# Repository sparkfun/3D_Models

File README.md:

3D Models for SparkFun Products!
----------------

This is a repository of basic geometry and source CAD files for 3D models that appear on our website. Models are stored in real world (1x) scale. STL units are millimeters.

_If you are using [eagleUp](https://eagleup.wordpress.com/) be sure to only export ```Place``` layers_

## Directory Structure

Folders and file names must only use a-z, - and _

#### Product Geometry Model Structure:
```
products/{product_id}/{rev_if_applicable}/{file_type}/

Ex:
products/12099/iges/12099.iges
products/12099/step/12099.step
products/12099/stl/12099.stl

If there were any revisions for this product_id:
products/11113/rev_1.0/stl/11113.stl
products/11113/rev_1.1/stl/11113.stl
```

#### Source Model Structure:
```
products/{product_id}/{rev_if_applicable}/source_{software}/

Ex:
products/11763/source_solidworks/model.sldprt

If there were any revisions for this product_id:
products/11763/rev_1.0/source_solidworks/11763.sldprt
products/11763/rev_1.1/source_solidworks/11763.sldprt

```

#### Product Display Structure:
We can display any combination of stl or json with textures
```
products/{product_id}/display/modela.stl

Ex:
products/8601/display/8601a.stl
products/8601/display/8601b.json
products/8601/display/8601b_texture.png
```

## Blender Common Display Materials

_Use the io_three blender addon in the https://github.com/mrdoob/three.js repository to export textured display models for our site_

_Be sure to set your scene's display device to none before export to prevent colors from being gamma corrected. Or use the startup file in this repo._

For composite display models, commit the blender file with separate objects for easy tweaking in the future. Combine the geometry before exporting to json.

#### Copper
```
Diffuse:  #DF8D38 Intensity: 0.8
Specular: #FFB730 Intensity: 0.5
Hardness: 100
```

#### Leads
```
Diffuse:  #FFFFFF Intensity: 0.8
Specular: #E6E6E6 Intensity: 0.5
Hardness: 100
```

#### Black Plastic (Headers)
```
Diffuse:  #000000 Intensity: 0.8
Specular: #A5A5A5 Intensity: 0.5
Hardness: 50
```

#### Black Metal 
```
Diffuse:  #000000 Intensity: 0.8
Specular: #505050 Intensity: 0.5
Hardness: 50
```

#### Black Chips
```
Diffuse:  #000000 Intensity: 1.0
Specular: #222222 Intensity: 0.5
Hardness: 50
```

#### SFE Red Silk
_Solid Material_
```
Diffuse:  #98041C Intensity: 1.0
Specular: #98041C Intensity: 0.5
Hardness: 50
```
_Textured Material_ (Red)
```
Diffuse:  #FF2835 Intensity: 0.8
Specular: #98041C Intensity: 0.5
Hardness: 50
```

#### Blue Plastic (Screw Terminals)
```
Diffuse:  #0000FF Intensity: 0.8
Specular: #0000A5 Intensity: 0.5
Hardness: 50
```

#### White Plastic
```
Diffuse:  #FFFFFF Intensity: 0.8
Specular: #E2E2E2 Intensity: 0.8
Hardness: 25
```

#### Grey Plastic
```
Diffuse:  #8A8A8A Intensity: 1.0
Specular: #FFFFFF Intensity: 0.25
Hardness: 50
```

#### Yellow Plastic (Li-ion Battery)
```
Diffuse:  #CC9D00 Intensity: 0.8
Specular: #FFD700 Intensity: 0.5
Hardness: 50
```

#### SMD Resistor Brown
```
Diffuse:  #8F5A24 Intensity: 0.8
Specular: #FFB730 Intensity: 0.5
Hardness: 100
```

#### Component Black
```
Diffuse:  #111111 Intensity: 0.8
Specular: #222222 Intensity: 0.5
Hardness: 100
```

#### Green Protoboard
```
Diffuse:  #00703D Intensity: 0.8
Specular: #0A5D19 Intensity: 0.5
Hardness: 100
```

#### TH Resistor
```
Diffuse:  #DBB37B Intensity: 0.8
Specular: #FFBA59 Intensity: 0.5
Hardness: 100
```

#### Yellow Tinted (SMD LED) 
```
Diffuse:  #CCC48E Intensity: 0.8
Specular: #FFFAD1 Intensity: 0.5
Hardness: 100
```

#### Blue PCB (Arduino)
```
Diffuse:  #0C457C Intensity: 0.8
Specular: #0F4E7A Intensity: 0.5
Hardness: 50
```

#### Lilypad
```
Hex for Lilypad 0x8000FF (purple)
```

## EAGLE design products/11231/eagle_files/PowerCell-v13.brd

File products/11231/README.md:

Models generated from [these file(s)](C:\Users\elizabeth.robert\Documents\GitHub\3D_Models\products\11231\eagle_files\PowerCell-v13.brd) using EagleUp on 12/02/16 at 16:47:00 -07:00

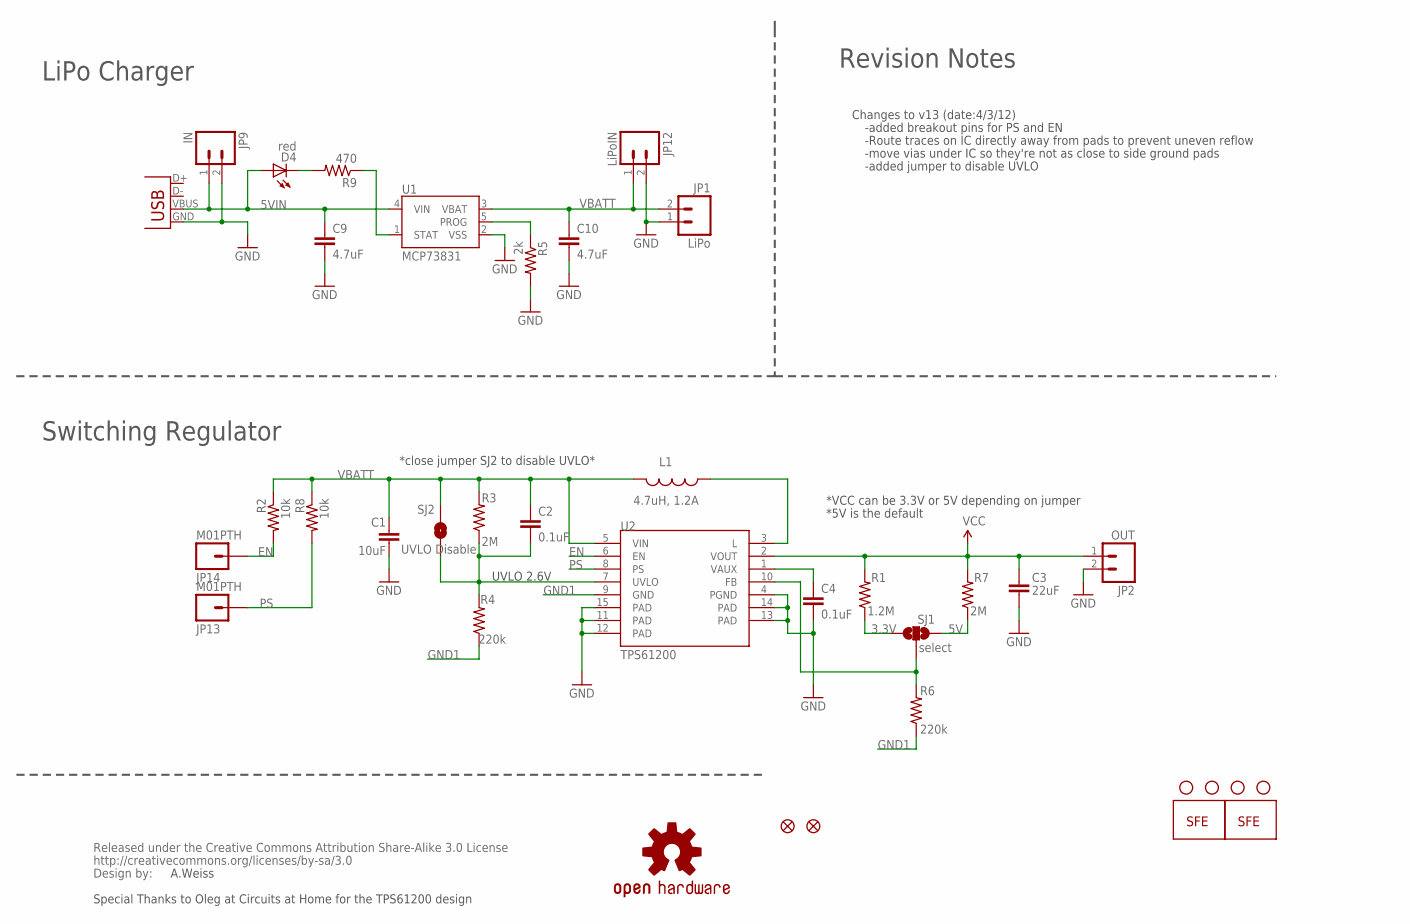
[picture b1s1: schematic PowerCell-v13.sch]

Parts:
C1: 10uF; 1206
C2, C4: 0.1uF; 0402-CAP
C3: 22uF; 0805
C9, C10: 4.7uF; 0402-CAP
D4: red; LED-0603
JP1: LiPo; JST-2-SMD
JP2: OUT; 1X02
JP3: LOGO-SFENEW; SFE-NEW-WEBLOGO
JP4: LOGO-SFESK; SFE-LOGO-FLAME
JP5, JP6, JP7, JP8: STAND-OFF
JP9: IN; 1X02
JP12: LiPoIN; 1X02
JP13, JP14: M01PTH; 1X01
JP15, JP16: FIDUCIALUFIDUCIAL; MICRO-FIDUCIAL
L1: 4.7uH, 1.2A; CDRH2D09
R1: 1.2M; 0402-RES
R2, R8: 10k; 0402-RES
R3, R7: 2M; 0402-RES
R4, R6: 220k; 0402-RES
R5: 2k; 0402-RES
R9: 470; 0402-RES
SJ1: select; SJ_3_PASTE2&3
SJ2: UVLO Disable; SJ_2S-NO
U1: MCP73831; SOT23-5
U2: TPS61200; QFN-10_PAD
U$1: OSHW-LOGOS; OSHW-LOGO-S
U$2: CREATIVE_COMMONS
X1: USB-MICROB

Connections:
3.3V: R1.1, SJ1.1
5V: R7.1, SJ1.3
5VIN: C9.1, D4.A, JP9.1, U1.4 (VIN), X1.VBUS
EN: JP14.1, R2.2, U2.6 (EN)
FB: R6.2, SJ1.2, U2.10 (FB)
GND: C1.2, C3.2, C4.2, C9.2, C10.2, JP1.1, JP2.2, JP9.2, JP12.2, R5.2, U1.2 (VSS), U2.4 (PGND), U2.11 (PAD), U2.12 (PAD), U2.13 (PAD), U2.14 (PAD), U2.15 (PAD), X1.GND
GND1: R4.1, R6.1, U2.9 (GND)
unnamed: C4.1, U2.1 (VAUX)
unnamed: L1.P$1 (1), U2.3 (L)
unnamed: D4.C, R9.2
unnamed: R5.1, U1.5 (PROG)
unnamed: R9.1, U1.1 (STAT)
PS: JP13.1, R8.2, U2.8 (PS)
UVLO: C2.2, R3.1, R4.2, SJ2.1, U2.7 (UVLO)
VBATT: C1.1, C2.1, C10.1, JP1.2, JP12.1, L1.P$2 (2), R2.1, R3.2, R8.1, SJ2.2, U1.3 (VBAT), U2.5 (VIN)
VCC: C3.1, JP2.1, R1.2, R7.2, U2.2 (VOUT)

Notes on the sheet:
UVLO 2.6V
Changes to v13 (date:4/3/12)
-added breakout pins for PS and EN
-Route traces on IC directly away from pads to prevent uneven reflow
-move vias under IC so they're not as close to side ground pads
*close jumper SJ2 to disable UVLO*
-added jumper to disable UVLO
A.Weiss
Special Thanks to Oleg at Circuits at Home for the TPS61200 design
LiPo Charger
Switching Regulator
Revision Notes
*VCC can be 3.3V or 5V depending on jumper
*5V is the default

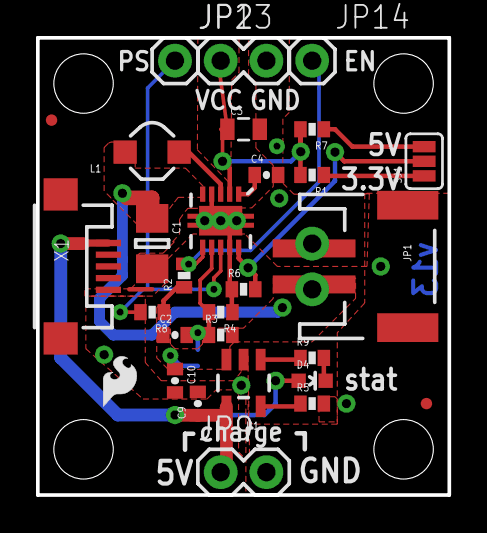
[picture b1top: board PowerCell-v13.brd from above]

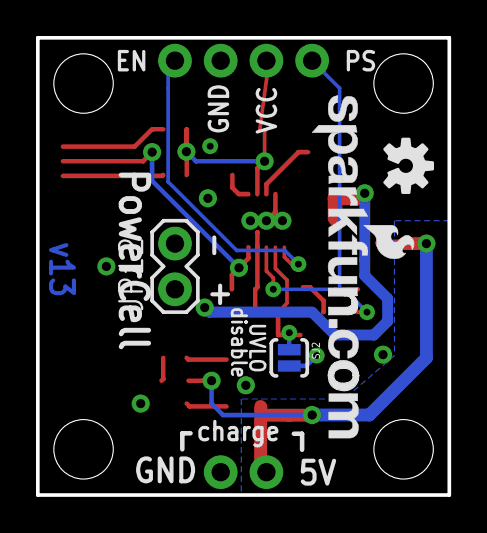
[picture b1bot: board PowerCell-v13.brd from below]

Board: 2 copper layers, 22.9 x 25.4 mm, 38 parts (4 on the bottom side), 16 nets.

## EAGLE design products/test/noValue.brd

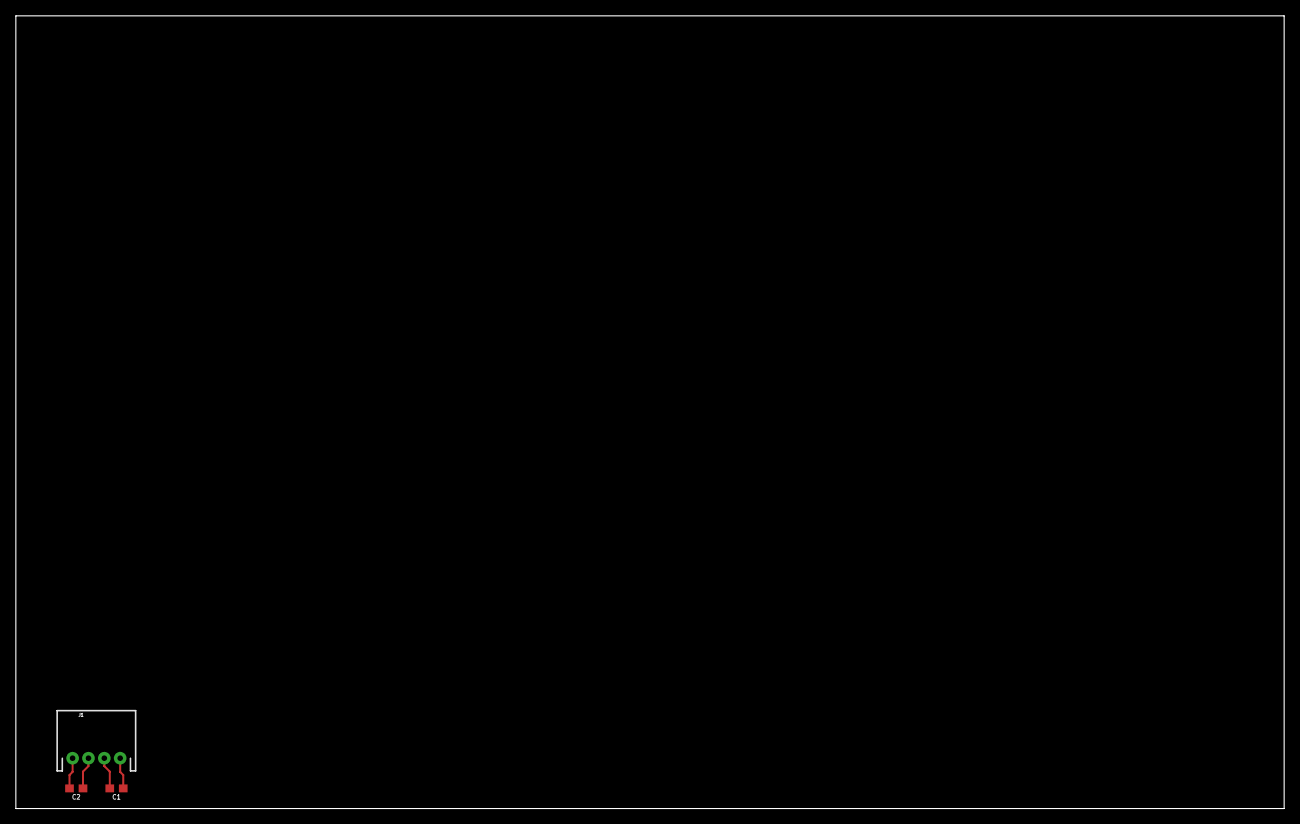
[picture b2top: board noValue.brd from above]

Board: 2 copper layers, 160.0 x 100.0 mm, 3 parts (0 on the bottom side), 4 nets.

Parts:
C1, C2: 0.1uF; 0603
J1: M04JST-PTH; JST-4-PTH

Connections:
unnamed: C2.1, J1.2
unnamed: C1.2, J1.3
unnamed: C1.1, J1.4
unnamed: C2.2, J1.1

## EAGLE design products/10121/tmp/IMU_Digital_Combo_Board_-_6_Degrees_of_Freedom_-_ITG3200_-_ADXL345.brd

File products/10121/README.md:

Models generated from [these file(s)](https://raw.github.com/sparkfun/IMU_Digital_Combo_Board/ea42199ef930084c266f158df344216c9f821b62/Hardware/IMU_Digital_Combo_Board%20_-_6_Degrees_of_Freedom_-_ITG3200_-_ADXL345.brd) using EagleUp on 03/24/16 at 9:38:12 -06:00

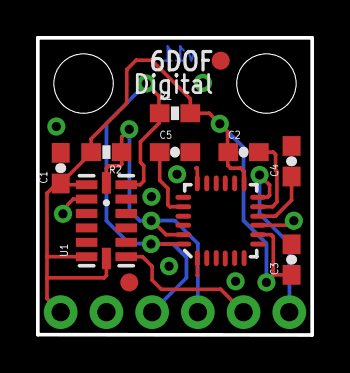
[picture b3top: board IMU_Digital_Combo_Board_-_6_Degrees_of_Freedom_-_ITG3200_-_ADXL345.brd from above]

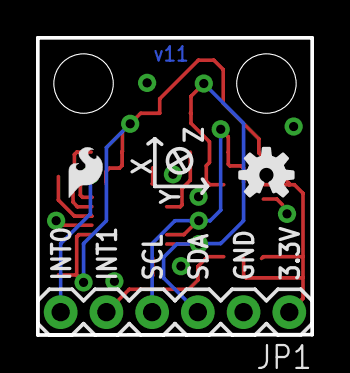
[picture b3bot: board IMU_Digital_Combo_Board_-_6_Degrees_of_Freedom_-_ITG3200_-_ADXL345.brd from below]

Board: 2 copper layers, 15.2 x 16.5 mm, 18 parts (3 on the bottom side), 8 nets.

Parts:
C1, C2, C4: 0.1uF; 0603-CAP
C3: 10nF; 0603-CAP
C5: 2.2nF; 0603-CAP
FRAME1: FRAME-LETTER; CREATIVE_COMMONS
JP1: 1X06
JP2, JP5: STAND-OFF
JP3: LOGO-SFESK; SFE-LOGO-FLAME
JP4, JP6: FIDUCIAL1X2; FIDUCIAL-1X2
R1: 4.7K; 0603-RES
R2: 4.7k; 0603-RES
U1: ADXL3451:1; LGA14
U3: ITG-32001:1; QFN-24_ITG3200_1:1
U$1: REVISION
U$2: OSHW-LOGOS; OSHW-LOGO-S

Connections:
3.3V: C1.1, C2.1, C3.1, JP1.1, R1.2, R2.2, U1.1, U1.6, U1.7, U3.8, U3.13
GND: C1.2, C2.2, C3.2, C4.2, C5.2, JP1.2, U1.2, U1.4, U1.5, U1.12, U3.1, U3.9, U3.11, U3.18
INT0: JP1.6, U3.12
INT1: JP1.5, U1.8
unnamed: C5.1, U3.20
unnamed: C4.1, U3.10
SCL: JP1.4, R2.1, U1.14, U3.23
SDA: JP1.3, R1.1, U1.13, U3.24

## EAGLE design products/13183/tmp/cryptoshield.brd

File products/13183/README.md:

Models generated from [these file(s)](https://raw.github.com/sparkfun/CryptoShield/c7040a1c54c259d4d555ea0fb823fd5dfa6bb8f8/Hardware/cryptoshield.brd) using EagleUp on 03/24/16 at 10:58:54 -06:00

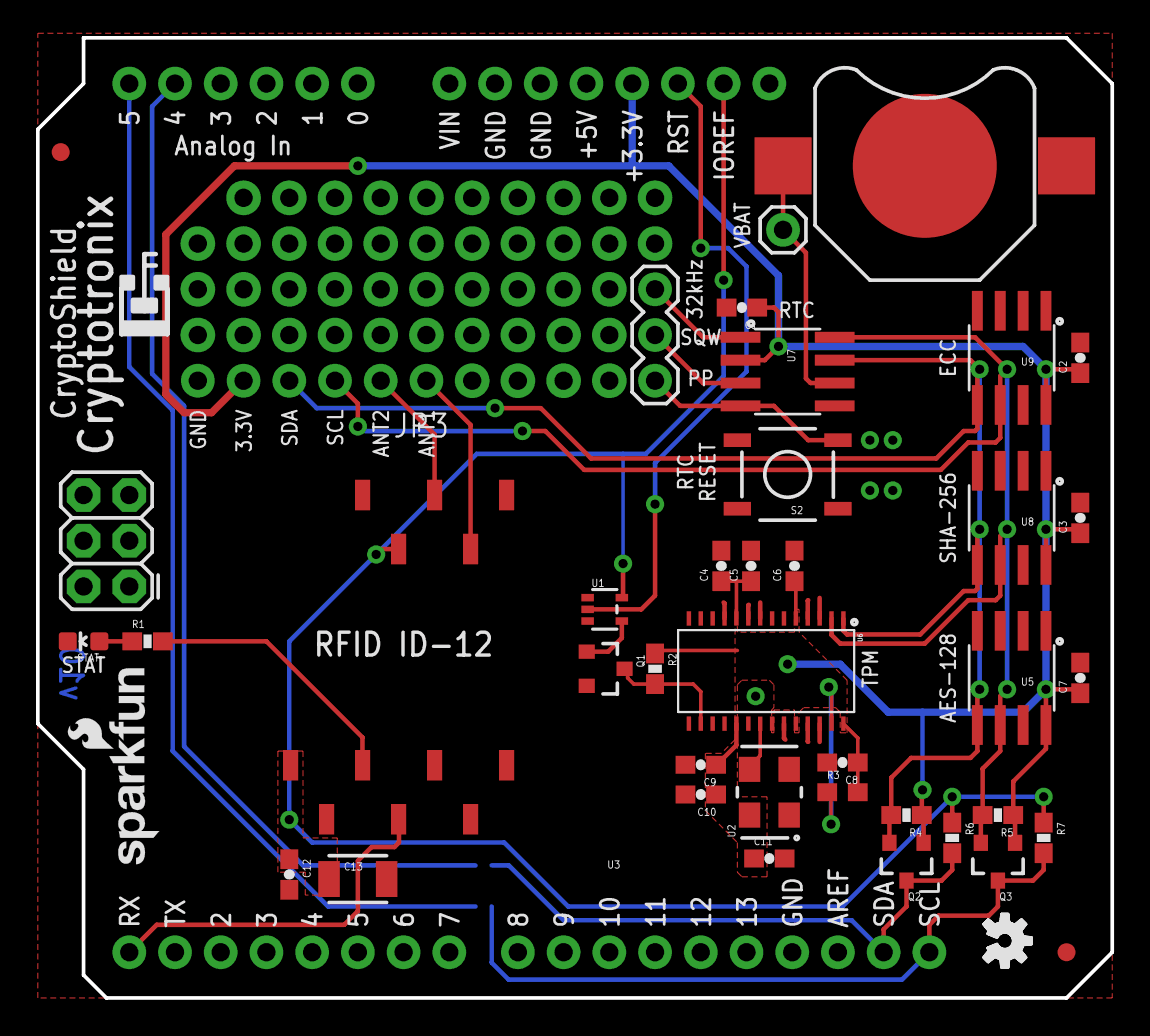
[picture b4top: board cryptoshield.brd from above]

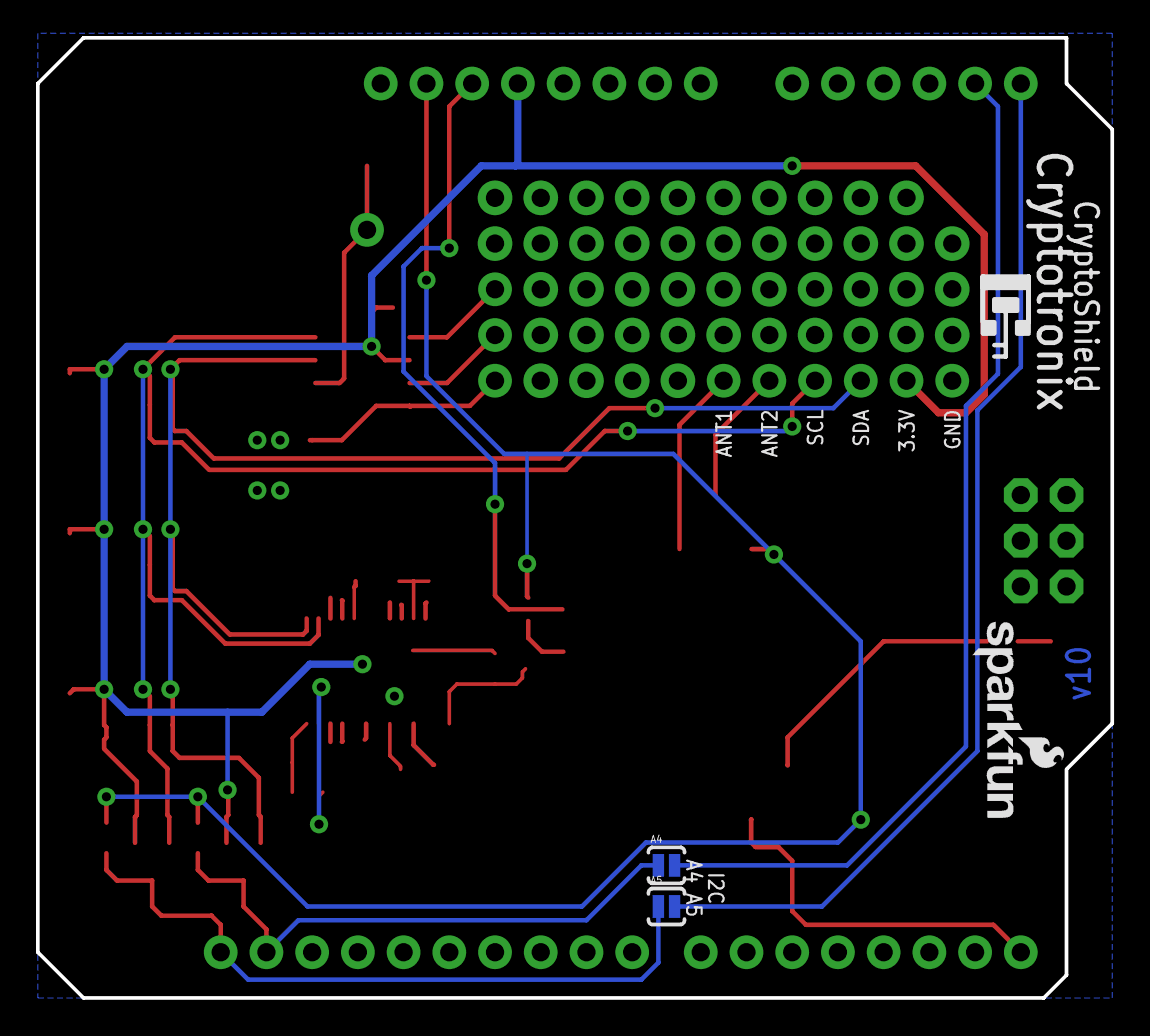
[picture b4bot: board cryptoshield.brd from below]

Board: 2 copper layers, 59.7 x 53.3 mm, 48 parts (3 on the bottom side), 23 nets.

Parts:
A4, A5: PAD-JUMPER-2-NO_YES_SILK
BAT1: 3V; BATTCON_12MM
C1, C2, C3, C7, C12: 0.1uF; 0603-CAP
C4, C10, C11: .1uf; 0603-CAP
C5, C6, C8, C9: 2200pf; 0603-CAP
C13: 10uF; 1210
FID1, FID2: FIDUCIAL1X2; FIDUCIAL-1X2
FRAME2: CREATIVE_COMMONS
J1: AVR_SPI_PRG_6PTH; 2X3
JP1: M01PTH; 1X01
JP2: 1X03
JP3: 1X06_NO_SILK
LOGO2: OSHW-LOGOS; OSHW-LOGO-S
LOGO3: SFE_LOGO_NAME_FLAME.1_INCH; SFE_LOGO_NAME_FLAME_.1
Q1, Q2, Q3: BSS138; SOT23-3
R1: 1k; 0603-RES
R2, R4, R5, R6, R7: 10K; 0603-RES
R3: 4.7K; 0603
S2: Reset; TACTILE-SWITCH-SMD
STAT: GREEN; LED-0603
U1: 74LVC1G04; SOT353
U2: 33mhz; CRYSTAL-OSC-SMD-5X3.2
U3: ID-12/20SMD; ID-12_SMD
U4: ARDUINO_R3_SHIELD; UNO_R3_SHIELD
U5: ATAES132; SOIC8
U6: AT97SC3204T; TSSOP28
U7: DS3231M; SOIC8
U8: ATSHA204_SOIC8; SOIC8
U9: ATECC108; SOIC8
U$3: OSHW-LOGO-S
U$101: SFE_LOGO_NAME_FLAME_.1

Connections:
3.3V: C1.1, C2.1, C3.1, C4.1, C5.1, C6.1, C7.1, C8.1, C9.1, C10.1, C11.1, JP3.5, Q2.1, Q3.1, R2.1, R3.2, R4.1, R5.1, U2.4, U4.3.3V, U5.8, U6.5, U6.10, U6.19, U6.22, U6.24, U6.28, U7.2, U8.8, U9.8
32KHZ: JP2.1, U7.1
!RESET: U1.2, U4.RES
ANT1: JP3.2, U3.3
ANT2: JP3.1, U3.4
GND: BAT1.GND, C1.2, C2.2, C3.2, C4.2, C5.2, C6.2, C7.2, C8.2, C9.2, C10.2, C11.2, C12.2, C13.2, JP3.6, Q1.2, S2.1, STAT.C, U1.3, U2.2, U3.1, U3.7, U4.GND@0, U4.GND@1, U4.GND@2, U5.4, U6.3, U6.4, U6.8, U6.9, U6.11, U6.15, U6.17, U6.18, U6.20, U6.23, U6.25, U6.26, U7.5, U8.4, U9.4
unnamed: R1.2, U3.10
unnamed: A4.2, U4.A4
unnamed: A5.2, U4.A5
unnamed: R1.1, STAT.A
unnamed: Q1.3, R2.2, U6.16
unnamed: R3.1, U6.27
unnamed: Q1.1, U1.4
PP: JP2.3, S2.3, U7.4
RX: U3.9, U4.RX
SCL: JP3.3, Q3.2, R5.2, U5.6, U6.2, U7.8, U8.6, U9.6
SCL_IN: A5.1, Q3.3, R7.2, U4.SCL
SDA: JP3.4, Q2.2, R4.2, U5.5, U6.1, U7.7, U8.5, U9.5
SDA_IN: A4.1, Q2.3, R6.2, U4.SDA
SQW: JP2.2, U7.3
TPM_CLK: U2.3, U6.21
VBAT: BAT1.PWR@1, JP1.1, U7.6
VCCIO: C12.1, C13.1, R6.1, R7.1, U1.5, U3.2, U3.11, U4.IOREF

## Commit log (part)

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2015-02-05 #8619 - Wombat
2015-02-05 #8467 - Lilypad TriColor
2015-02-05 EIA3528 production part
2015-02-05 #10899 - LilyTiny
2015-02-05 #11893 - Lilypad SimplePower
2015-02-05 eagleUp update
2015-02-05 #9238 - fix a couple missing mats
2015-02-05 #11364 - LilyTwinkle
2015-02-13 Updated packages for big easy. Relocated diodes to semiconductors.
    Updated Packages:
    SO-214/SMA-DIODE
    QFN-28
    SOT-89 Copy
    3mm Trimpot
    2010 resistor fuse
2015-02-13 12859 Big Easy Driver revision
2015-02-14 Time of Flight Range Finder Breakout 12784
2015-02-14 Time of Flight Range Finder Sensor 12785
2015-02-16 rebuild promicro boards to fix bottom texture
2015-02-17 #10030 XBEE Header
2015-02-17 xbee-smd production part
2015-02-17 fix pads D pad to C pad
2015-02-17 fix header D pad to C pad
2015-02-17 update MICRO-B connector
2015-02-17 MagJack Breakout 13021
2015-02-17 MagJack RJ-45 Connector 8354
2015-02-18 #11520 - Arduino Fio
2015-02-18 #11373 - XBee Explorer
2015-02-18 #11812 - XBee Explorer
2015-02-18 #12731 - FT232R Breakout
2015-02-19 #9966 - USB Mini B
2015-02-24 #10401 - SparkFun Lipo Charger
2015-02-25 magjack updates
2015-03-31 Updated Passives, Connectors, and Switches
2015-03-31 12633 IOIO OTG
2015-03-31 12779 Easy Driver
2015-03-31 13058 MiP Pro Mini
2015-03-31 13116 Spectrum Shield
2015-03-31 13120 Cellular Shield (Stub)
2015-04-02 Connectors - Added SIMHOLDER, BATTCON_12mm, and headers for ID-12 connection
2015-04-02 Added MG2639
2015-04-02 PTH Components for Kits
2015-04-02 Added IC Pkgs: SOT353, TO263, TSSOP28
2015-04-03 10592 Coin Cell Battery Holder - 12mm SMD
2015-04-03 12959 MOSFET Power Control Kit
2015-04-03 13118 Servo Trigger
2015-04-03 13183 Cryptoshield
2015-04-03 12320 HX711 Load Cell Amplifier
2015-04-03 08084 2-terminal Screw Terminal
2015-04-03 08235 3-terminal Screw Terminal
2015-04-03 readme
2015-04-09 11678 - RN-52 Bluetooth Module
2015-04-09 12849 - RN-52 Breakout board
2015-04-10 ML8511 UV sensor
2015-04-10 12705 UV breakout board
2015-04-29 README typo fix
    Fixed a typo in the main README.
2015-04-29 Five 5mm LEDs
    + Added COM-9590 (LED - Basic Red 5mm)
    + Added COM-9592 (LED - Basic Green 5mm)
    + Added COM-9594 (LED - Basic Yellow 5mm)
    + Added COM-11372 (LED - Basic Blue 5mm)
    + Added COM-12704 (LED - Violet 5mm)
    I had made these before, but I redid them with Blender (they were SKPs
2015-04-29 Optical Detectors
    + Added SEN-00241 (Infrared Emitters and Detectors) NOTE: the .blend
    has the two parts separate, but the .stl and .json have them together.
    + Added SEN-00246 (Optical Detector / Phototransistor - QRD1114)
    + Added SEN-09088 (Mini Photocell)
    + Added SEN-09299 (Photo Interrupter - GP1A57HRJ00F)
    + Added SEN-10266 (IR Receiver Diode - TSOP38238)
2015-04-30 More size changes
    The last size change, for the ALS-PT19 Light Sensor.
2015-05-06 11015 Small solenoid
2015-05-20 Bluetooth BLE mate2
2015-05-20 11840 LED Holder - 5mm
2015-05-20 548 Sim Card Holder (added and deleted files)
2015-05-20 8235 Screw Terminal (file cleanup)
2015-05-20 13169 Blackberry Trackballer
2015-05-20 9032 Thumb Joystick
2015-06-05 Update to readme
2015-06-05 429 - DB9 connector, Female
2015-06-05 11895 - Header 1x8 Female PTH
2015-06-05 11896 - 1x10 Header Female, PTH
2015-06-05 119 - DC Power Barrel Jack
2015-06-05 13099 - Rotary Switch Pot Breakout
2015-06-05 13229 - FreeSoC Dev Board
2015-08-19 Production Parts - Connectors
2015-08-19 13655 needs fix
2015-08-19 Production Parts - Passives
2015-08-19 Production Parts - ICs: 16LPCC LGA14L LGA24 SI470X SOIC8 - SO08 alternate
2015-08-19 Production Parts - Stomp Switches
2015-08-19 11366 - Big Red Box (WIP)
2015-08-19 12938 - Si4703 Eval
2015-08-19 13268 - Snappable Proto Board (Needs Fix)
2015-08-19 13284 LSM9DS1
2015-08-19 13339 - LSM6DS3
2015-08-19 unreleased (WIP)
2015-08-19 9238 - Stepper motor (artifact)
2015-08-26 731 110mAh lipo battery
2015-08-26 Cleanup - 246
2015-08-26 1x12 SMD Connector for photon system
2015-08-26 corrected reference data on connectors
2015-08-26 6mm PTH pushbutton
2015-08-26 IC packages
2015-08-26 connector set for photon system
2015-08-26 RJ11 connector, 6-pin
2015-08-26 ICs for production assemblies
2015-08-26 97 - 6mm PTH pushbutton
2015-08-26 13038 - Edison GPIO block
2015-08-26 13044 - Edison Raspberry Pi Block
2015-08-26 132 - RJ11 6-pin connector
2015-08-26 13328 - Photon Wearable Shield
2015-08-26 13344 - Header, Female, 12-pin, SMD
2015-08-26 13626 - Photon Battery Shield
2015-08-26 13629 - Photon IMU Shield
2015-08-26 13630 - Photon Weather Shield
2015-09-24 11351 Aluminum enclosure updates
2015-09-24 11366 Big Red Box changes and updates
2015-09-24 13683 SHT15 Humidity/Temperature Sensor Breakout
2015-09-24 Proto Petal (development)
2016-01-20 Production Parts
2016-01-20 11366 basic, and with hole patterns
2016-01-20 Updates to 12481 and 12558
2016-01-20 13155
2016-01-20 13266
2016-01-20 13664
2016-01-20 13672
2016-01-20 13711
2016-01-21 Production Parts: Audio Jack mod, SOIC28, SSOP24
2016-01-21 13720 - incomplete, wrong .brd file
2016-02-01 9816 OpAmp Breakout
2016-02-01 Production Parts Additions
    C0402
    TRIMPOT-3MM Name Clone from TRIMPOT-3MM-2
2016-02-03 additions to production_parts and products
2016-02-09 production_parts additions and revisions
2016-02-09 11927 BC127 Breakout
    Board Addition
2016-02-10 13033 9DOF and LGA-24 Additions
2016-02-11 13037 Block for Intel Edison Battery Addition
2016-02-11 10524 Atmega328 Optiboot Uno
2016-02-17 10217 LiPo Charger Basic
2016-02-22 13175 Gripper Kit B
2016-02-24 10124 RS485 Breakout Board
2016-02-29 10975 Surface Transducer Large
2016-03-01 Production Parts Additions
2016-03-03 13174 Standard Gripper Kit A
2016-03-03 Minor Updates: Two Deleted Files and README Mod
2016-03-07 8184 Surface Mount Navigation Switch
2016-03-09 11969 Metal Pushbutton Yellow Momentary
2016-03-09 11974 Metal Pushbutton Yellow Latching
2016-03-09 11966 Metal Pushbutton Red Momentary
2016-03-09 11971 Metal Pushbutton Red Latching
2016-03-09 11968 Metal Pushbutton Green Momentary
2016-03-09 Json File Updates to Products 11966 and 11971
2016-03-09 11967 Metal Pushbutton Blue Momentary
2016-03-09 11975 Metal Pushbutton White Latching
2016-03-09 11970 Metal Pushbutton White Momentary
2016-03-09 552 Battery Holder 4xAA
2016-03-10 9378 AVR 8 Pin ATtiny85
2016-03-10 9378 STL Update
2016-03-14 11441 7 Segment Display Product and Part
2016-03-14 11442 7 Segment Display Blue
2016-03-14 11440 7 Segment Display Kelly Green
2016-03-14 11629 7 Segment Display White
2016-03-16 Removal of Spaces from File Names
2016-03-16 Repo Clean Up Deleting Duplicates with Spaces
2016-03-16 Repo Clean Up of File Names
2016-03-24 Production_parts Cleanup of Files
2016-03-24 Repo Cleanup
2016-03-24 Production Parts Updates
2016-03-24 ignore tmp files from builder
2016-03-24 Fixes to Display Models
2016-03-30 Display Changes 2
2016-03-30 Display Change and Additions
2016-03-30 organizing
2016-03-30 Production Parts Changes
2016-03-30 Production Part Organization
2016-03-30 Product changes
2016-03-30 Display File Clean Up
2016-04-01 test
2016-04-01 Color Changes to Display Files
2016-04-05 Display color changes to products
2016-04-05 8483 Product Addition Li-ion 2000mAh
2016-04-06 Product Display Changes
2016-04-07 Display changes and updates
2016-04-12 Product 12171 Display Changes
2016-04-25 Product 13813 Li-ion 1000mAh
2016-04-27 11288 Heating Pad 5x10 cm
2016-04-27 12923 SparkFun MicroView
2016-04-28 Only json added for now
2016-05-02 Product 13733 Display Addition
2016-05-03 Product 12291 change and display repo change
2016-05-03 Repo Display Changes
2016-05-06 Display Changes for Repo
2016-05-12 Products 13345 13764 13773
    To close out bug 12826
2016-05-12 13774 STL Orientation Change
2016-05-16 Display and File Name Changes
2016-05-19 Product 11792
2016-05-19 11792 STL orientation change
2016-06-01 Product 12958 and Misc Components
2016-07-11 Products 9067 9068 9066
2016-08-11 Product 13687 MyoWare Cable Shield
2016-08-23 20 mm Coin Cell Battery Holder
2016-08-23 Product 13584 MyoWare Power Shield plus Coin Cell 20 mm Fix
2016-09-15 LED5MM addition
2016-09-15 Spaces removed from files
2016-09-26 Moved to Products Folder
2016-09-27 13723 Display Additions for MyoWare Muscle Sensor
2016-09-28 Product 10976 10K Slide Pot
2016-10-19 Product 11886
2016-10-25 Change of 9395 LCD
2016-10-25 File changes made for storefront display
2016-10-25 Product 9394 16x2 Serial LCD White on Black
2016-10-25 Product 9393 16x2 LCD Black on Green and Changes
2016-11-17 Additions to Production Parts Folder
    QFN-48 and SC70
2016-11-17 Product 13907 ESP32 Thing
2016-11-17 Product 13678 WiFi Module ESP8266
2016-11-18 Products 13124 and 13967
    Protopedal and Case
2016-11-18 Product 13884 LED Driver Breakout
2016-11-22 Product 13990 and some Production_Parts Additions
2016-11-22 Product 13911 Serial Controlled Motor Drive plus Production_Parts
2016-11-23 Product 13944 9DoF Sensor Stick
2016-11-23 Prorduct 13879 Load Cell Amp and SSOP16L
2016-11-23 Products 12758 Electret Mic Breakout and 8635 Electret Mic
2016-11-23 Product 13118 Servo Trigger and Product 13872 Cont Servo Trigger
2016-11-23 Product 13231 ESP8266 Thing
2016-11-29 Product 13777 Battery Babysitter plus Production Parts created
2016-11-30 Product 13762 3D Model
2016-12-02 Product 13261 Open Scale and Production_Parts Additions
2016-12-02 Product 12231 OpenScale and Production Parts
2016-12-02 Product 11231 Power Cell LiPo and Production Parts
2016-12-07 Add seemingly successfully generated STL files previously missing.
    Generated via batch operation, verified sane-looking with Pleasant3D.
2016-12-07 Add previously missing generated STL file. Possibly upside down.
    Generated via batch operation, appears upside down with Pleasant3D.
2016-12-07 Produt 13762 MPU 9250
2016-12-12 Production Part Additions
2016-12-12 Product 14001 9DOF Razor
2016-12-14 Product 13926 Triple Axis MMA8452Q plus Production Part
2016-12-27 Removal of .json 258
2016-12-27 Product 13733 Raspberry Pi LCD Dimension Changes
2016-12-27 Product 498 SSOP to DIP Adapter 16 Pin
2016-12-27 Product 499 SparkFun SSOP to DIP Adapter 20 Pin
2016-12-27 Product 544 microSD Breakout
2016-12-27 Product 527 Voltage Regulator Adjustable
2016-12-27 Product 691 SparkFun Transceiver Breakout - nRF24L01+
2016-12-29 Product 717 DIP Adapter
2016-12-29 Product 762 USB Bit Whacker
2016-12-29 Product 8276 SparkFun XBEE Breakout
2016-12-29 Product 8688 TEMPT6000 Breakout
2016-12-29 Product 8883 ACS712 Low Current Sensor Board
2017-01-09 Product 11864 Deans Male and Female
2017-01-09 Product 13963 LIS3DH Breakout
2017-01-10 Product 9277 2x2Button Pad Breakout
2017-01-10 Product 9116 PhotoInterrupter Breakout
2017-01-10 Product 9419 MicroSD Sniffer
2017-01-10 Product 9536 5 Pin Din Female
2017-01-11 Product 9716 FTDI Basic 5V
2017-01-16 Product 790 16X2 LCD Display
2017-01-16 Product 12642 Sound Detector and SOD-523
2017-01-17 Product 12002 Breadboard White
2017-01-17 Product 12062 5mm LEDs
2017-01-19 Add new batch of exported models.
    These have been verified as not being obviously wrong via Pleasant3D viewer.
2017-01-19 Add another generated STL file. Faulty, missing a face.
2017-01-19 Dimension Issue Fix for Part QFN24-3X3
2017-01-23 Hopefully completes previous merge. Case sensitivity issue.
    New file from merge had a capitalised `.STL` extension so it
    was missed on OS X.
    File in question: production_parts/semiconductors/IC_SMD/QFN/QFN-24/stl/QFN24-3X3.STL
2017-01-23 Attempt to deal with case sensitivity issue.
    Deleting old file via GitHub web interface.
2017-01-23 Add new STL export for SF model update.
2017-01-23 Remove obsolete model.
2017-01-24 Resistor Products
    11507 and 8377 - 300 Ohm Resistor
    11508 and 8374 - 10K Ohm Resistor
2017-02-21 Product 12757 and 13975 Added and Fixed
2017-02-22 Fixing Display of MicroView OLED 12923
2017-02-22 Product 533 Red LED 3mm
2017-05-08 Product 13656 Main Files
2017-05-08 Changes to Display File
2017-06-15 Spectacle Button Board
2017-06-15 14052 Spectacle LED Control Board
2017-06-17 14034 Spectacle Audio Output Board
2017-06-17 13912 Spectacle Director Board
2017-06-17 13993 Spectacle Motion Board
2017-08-08 product 9347 servo motor
2017-08-09 product 13288 kit teensy

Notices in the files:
parts and their libraries:
SparkFun-Aesthetics: Licensing: CC v3.0 Share-Alike You are welcome to use this library for commercial purposes.
SparkFun-Aesthetics: Released under the Creative Commons Attribution Share-Alike 3.0 License
SparkFun-Aesthetics: http://creativecommons.org/licenses/by-sa/3.0
